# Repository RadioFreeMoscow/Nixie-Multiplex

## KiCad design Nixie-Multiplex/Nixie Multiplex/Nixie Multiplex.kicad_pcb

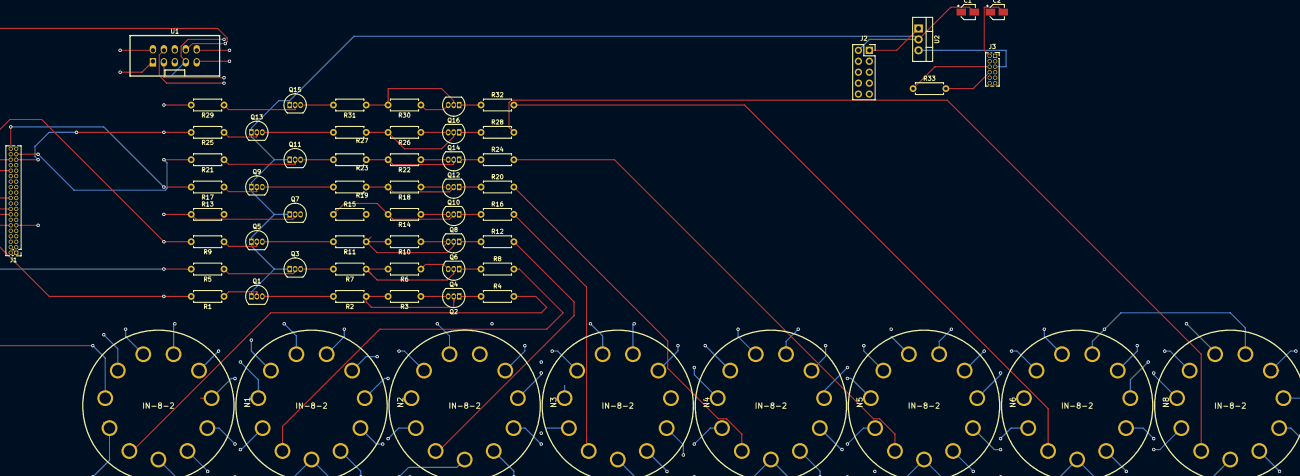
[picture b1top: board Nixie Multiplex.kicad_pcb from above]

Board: 2 copper layers, 64 parts (0 on the bottom side), 69 nets.

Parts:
C1, C2: CP; CP_Elec_3x5.3
J1: Connector-ML_RPi_GPIO; PinHeader_2x20_P1.27mm_Vertical
J2: Conn_2Rows-05Pins; PinSocket_2x05_P2.54mm_Vertical
J3: Conn_02x08_Top_Bottom; PinSocket_2x06_P1.27mm_Vertical
N1, N2, N3, N4, N5, N6, N7, N8: IN-8-2; nixies-us-IN-1
Q1, Q3, Q5, Q7, Q9, Q11, Q13, Q15: MPSA42; TO-92_Inline
Q2, Q4, Q6, Q8, Q10, Q12, Q14, Q16: MPSA92; TO-92_Inline
R1, R4, R5, R8, R9, R12, R13, R16, R17, R20, R21, R24, R25, R28, R29, R32: 10k; R_Axial_DIN0207_L6.3mm_D2.5mm_P7.62mm_Horizontal
R2, R7, R11, R15, R19, R23, R27, R31: 1M; R_Axial_DIN0207_L6.3mm_D2.5mm_P7.62mm_Horizontal
R3, R6, R10, R14, R18, R22, R26, R30: 10K; R_Axial_DIN0207_L6.3mm_D2.5mm_P7.62mm_Horizontal
R33: 330R; R_Axial_DIN0207_L6.3mm_D2.5mm_P7.62mm_Horizontal
U1: K155NA1; box_header_5x2
U2: LM7805_TO220; TO-220-3_Vertical

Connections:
+5V: C2.1, J3.5, U1.5, U2.3
A1: N1.A, R4.2
A2: N2.A, R8.2
A3: N3.A, R12.2
A4: N4.A, R16.2
A5: N5.A, R20.2
A6: N6.A, R24.2
A7: N7.A, R28.2
A8: N8.A, R32.2
GND: C1.2, C2.2, J2.2, J3.2, Q1.1, Q3.1, Q5.1, Q7.1, Q9.1, Q11.1, Q13.1, Q15.1, U2.2
N0: N1.0, N2.0, N3.0, N4.0, N5.0, N6.0, N7.0, N8.0
N1: N1.1, N2.1, N3.1, N4.1, N5.1, N6.1, N7.1, N8.1
N2: N1.2, N2.2, N3.2, N4.2, N5.2, N6.2, N7.2, N8.2, U1.8
N3: N1.3, N2.3, N3.3, N4.3, N5.3, N6.3, N7.3, N8.3, U1.9
N4: N1.4, N2.4, N3.4, N4.4, N5.4, N6.4, N7.4, N8.4
N5: N1.5, N2.5, N3.5, N4.5, N5.5, N6.5, N7.5, N8.5
N6: N1.6, N2.6, N3.6, N4.6, N5.6, N6.6, N7.6, N8.6
N7: N1.7, N2.7, N3.7, N4.7, N5.7, N6.7, N7.7, N8.7, U1.10
N8: N1.8, N2.8, N3.8, N4.8, N5.8, N6.8, N7.8, N8.8, U1.1
N9: N1.9, N2.9, N3.9, N4.9, N5.9, N6.9, N7.9, N8.9, U1.2
unnamed: C1.1, J3.1
unnamed: J1.12, R1.2
unnamed: J1.32, R5.2
unnamed: J1.33, R29.2
unnamed: J1.35, R25.2
unnamed: J1.36, R9.2
unnamed: J1.37, R21.2
unnamed: J1.40, R17.2
unnamed: J2.1, U2.1
unnamed: J3.6, R33.1
unnamed: J3.8, R33.2
unnamed: Q1.2, R1.1
unnamed: Q1.3, R2.2
unnamed: Q2.1, R4.1
unnamed: Q2.2, R2.1, R3.2
unnamed: Q2.3, R3.1
unnamed: Q3.2, R5.1
unnamed: Q3.3, R7.2
unnamed: Q4.1, R8.1
unnamed: Q4.2, R6.2, R7.1
unnamed: Q5.2, R9.1
unnamed: Q5.3, R11.2
unnamed: Q6.1, R12.1
unnamed: Q6.2, R10.2, R11.1
unnamed: Q7.2, R13.1
unnamed: Q7.3, R15.2
unnamed: Q8.1, R16.1
unnamed: Q8.2, R14.2, R15.1
unnamed: Q9.2, R17.1
unnamed: Q9.3, R19.2
unnamed: Q10.1, R20.1
unnamed: Q10.2, R18.2, R19.1
unnamed: Q11.2, R21.1
unnamed: Q11.3, R23.2
unnamed: Q12.1, R24.1
unnamed: Q12.2, R22.2, R23.1
unnamed: Q13.2, R25.1
unnamed: Q13.3, R27.2
unnamed: Q14.1, R28.1
unnamed: Q14.2, R26.2, R27.1
unnamed: Q15.2, R29.1
unnamed: Q15.3, R31.2
unnamed: Q16.1, R32.1
unnamed: Q16.2, R30.2, R31.1
RPIKIDA: J1.16, U1.3
RPIKIDB: J1.18, U1.6
RPIKIDC: J1.22, U1.7
RPIKIDD: J1.11, U1.4
VCC: Q4.3, Q6.3, Q8.3, Q10.3, Q12.3, Q14.3, Q16.3, R6.1, R10.1, R14.1, R18.1, R22.1, R26.1, R30.1

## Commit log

2021-01-29 Update
    Updated with new routing, and less sanity.
    Memes have been added as placeholder on silkscreen
